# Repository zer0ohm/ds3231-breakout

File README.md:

# ds3231-breakout
電源回路付DS3231用ブレークアウト基板

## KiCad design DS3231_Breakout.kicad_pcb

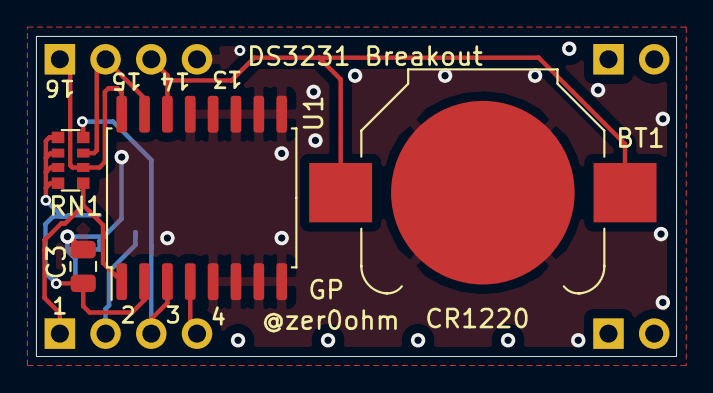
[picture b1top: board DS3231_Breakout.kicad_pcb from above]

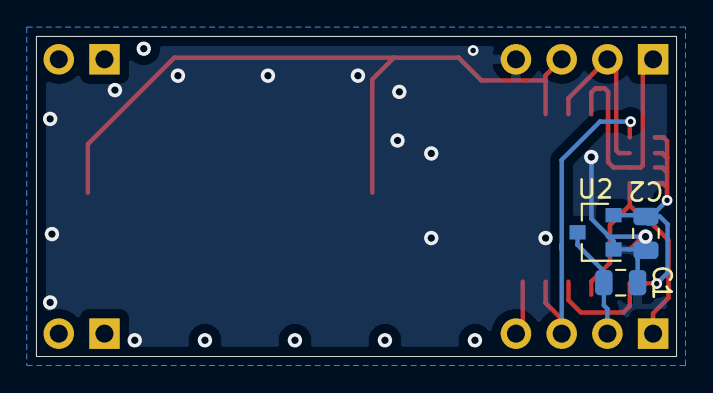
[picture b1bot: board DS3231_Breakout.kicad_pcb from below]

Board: 2 copper layers, 35.6 x 17.8 mm, 11 parts (3 on the bottom side), 9 nets.

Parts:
BT1: Keystone_3000; BatteryHolder_Keystone_3000_1x12mm
C1, C2: 1u; C_0805_2012Metric
C3: 0.1u; C_0805_2012Metric
CN1, CN2: Conn_01x04; PinHeader_1x04_P2.54mm_Vertical
CN3, CN4: Stand; PinHeader_1x02_P2.54mm_Vertical
RN1: 10k; R_Array_Convex_4x0612
U1: DS3231S; SOIC-16W_7.5x10.3mm_P1.27mm
U2: MCP1703AT; SOT-23

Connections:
+3V3: C2.1, C3.1, RN1.1, RN1.2, RN1.3, RN1.4, U1.2, U2.2
+BATT: BT1.1, CN2.3, U1.14
/RTC_32k: CN1.1, RN1.5, U1.1
/SCL: CN2.1, RN1.6, U1.16
/SDA: CN2.2, RN1.7, U1.15
/~INT: CN1.3, RN1.8, U1.3
/~RST: CN1.4, U1.4
GND: BT1.2, C1.2, C2.2, C3.2, CN2.4, U1.5, U1.6, U1.7, U1.8, U1.9, U1.10, U1.11, U1.12, U1.13, U2.1
VS: C1.1, CN1.2, U2.3

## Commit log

2020-10-24 設計データを追加
